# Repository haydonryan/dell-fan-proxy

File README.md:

# Dell Fan controller

Arduino Mega Fan Controller Sheild For R7515, R540 non hot swap fans.

# Background
I run an R7515 in my homelab. It's in a separate room upstairs (from my office) with the door open, I can hear it from my office downstairs.  It makes the room unusable that it sits in.

At 43% FAN, I can barely hear it from downstairs, 35% is really not too bad, up close.

The minimum fan speed and therefore noise is designed for a datacenter next to other heat generating servers with no noise contstraints, not a room in a house.
Plus I've got some non dell hardware( like many others do in homelabs) that the idrac controller doesn't know how to talk to, so the idrac just ramps the fans up to compensate for that one device.

I also noticed that at idle (which the machine sits 90% of the time) there is a 3 degree C differential between inlet and outlet temp, with the cpu being nice and cool.

# Why
- Dell support told me I'm not using the server for it's use case (Datacenter usage) - They're correct.
- Don't want to modify the firmware (it's signed anyways)
- Thought this would be an interesting project tom get more into electronics and control boards.

- As these machines come out of primary service in datacenters people are going to want to lab them - let's give them the power to do that!

# Disclaimer
- Will void your warranty
- Could cause your server to overheat
- Improper connection of fans can short out your motherboard!!!

- No responsibility taken for damaged hardware, loss of income, etc.

# Bill Of Materials:
- 6 Molex 2.00mm 2 Row, 6 Position Rectangular Receptical (Part # 0511100660) ~80c each https://www.digikey.com/en/products/detail/molex/0511100660/1144838?s=N4IgTCBcDaIOoFkCMAOArAdgwWgHIBEQBdAXyA
- 36 Molex Connector Socket 24-30AWG Crimp Gold (Part # 0503948054) 5c each https://www.digikey.com/en/products/detail/molex/0503948054/2404822?s=N4IgTCBcDaIAwFY4GYCcAWAHI9IC6AvkA

- 6 Amphenol ICC Conenctor Through Header Vert 6 Ppos 2.00mm (Part # 98414-G06-06LF) https://www.digikey.com/en/products/detail/amphenol-icc-fci/98414-G06-06LF/1535247?s=N4IgTCBcDaIGwAYCcBaAzHMAOFA5AIiALoC%2BQA

- 1 Arduino Mega

- 24 AWG hookup wire - 5 colors preferred, but just be careful if you don't have different colors Cheaper on Amazon (https://www.amazon.com/CBAZYTM-Stranded-Flexible-Silicone-Electric/dp/B073RD76QD/ref=sr_1_22?dchild=1&keywords=24%2BAWG&qid=1606865665&s=hi&sr=1-22&th=1)

- 6 TMP36 Temperature Sensors?? ~$1.50 https://www.digikey.com/en/products/detail/analog-devices-inc/TMP36GT9Z/820404

- Shrink wrap for wires
  - https://www.amazon.com/Eventronic-200pcs-Shrink-Tubing-Tubes/dp/B087JHB2CL/ref=sr_1_68?dchild=1&keywords=shrink+wrap+tube&qid=1606867076&sr=8-68
  - https://www.amazon.com/High-Heat-Shrink-Tubing-Tube/dp/B0722HN8SW/ref=sr_1_80?dchild=1&keywords=shrink+wrap+tube&qid=1606867076&sr=8-80
  - https://www.mouser.com/ProductDetail/Qualtek/Q2-F-RK4-1-16-11-6IN-39?qs=f6iYHOF0qgRLREW66g%2FPwg%3D%3D&gclid=CjwKCAiA8Jf-BRB-EiwAWDtEGuuEjQNy0toZvRLEwSUv5-1h-9RVMS_Smtxu-MWcHakHl9INQqu-WxoCvIEQAvD_BwE

# Random bits of information

By measuring and pulling pins out of the fan, I was able to determine that the pins (with the plastic nib up, facing away from you in the order:
```
1   2   3
4   5   6
```

That the Wires are:

1. Blue - PWM
2. Not connected
3. Black - Ground
4. -| Red - 12v (this wire continues to fan)
5. -| Red - 12v Loopback
6. Yellow - Sense wire.

Arduino Pin	 Register
- 2	OCR3B
- 3	OCR3C
- 4	OCR4C
- 5	OCR3A
- 6	OCR4A
- 7	OCR4B
- 8	OCR4C
- 9	OCR2B
- 10	OCR2A
- 11	OCR1A
- 12	OCR1B
- 13	OCR0A
- 44	OCR5C
- 45	OCR5B
- 46	OCR5A

source: http://astro.neutral.org/arduino/arduino-pwm-pins-frequency.shtml

## Fri Dec 31 11:26:19 2021
Checked the continuity - on the new server board - there's a common 12v rail AND common 12v ground.  This means that I can easily check the fan project using the bench power supply.

So far so good on the server. Printed U shaped spacers to save the cables for fans 1-3.  Definitely prefer to do this over not having anything pushing the top up.

I did find that only fan 3 has 12v power when powered off, the rest must be switched somewhere in the motherboard.

Cable lengths:
- Fan 1 30cm
- Fan 2 26cm
- Fan 3 45cm
- Fan 4 40cm
- Fan 5 35cm
- Fan 6 40cm

Max length shrink tubing at the arduino end: 1-1.5cm

# July 2022 Update
I've been testing this during summer and noticed that as the inlet temperature approaches the limit "for this configuration" the fans ramp significantly.  This is clearly a preventative reaction rather than a reactive one.  Also ensuring that the hardware that is in the server is "compatilbe" aka listed on the compatabilty matrix certainly helps to reduce the speed of the fans.

# May 2024 Update
Have been running my server 24/7 for two years now with no ill effects.  No hardware failures, and just less noise.  It's not perfect and fans seem to surge slightly vs stay flat consistently.  It's not too big of an issue and could probably be adjusted by increasing the time the fans are averaged. Very happy with how this project is running.

# Making cable tips.
Put some shrink tubing on the 12v wire on the loop and the main wire before putting the terminal into the block. Stray 12v is SUPER bad.
Cut the terminal off the tape but leave the small bit of tape on for holding it steady.
put the terminal into the 1.3mm crimp size first all the way up to the tape - it should hold itself in there - making it easier to feed in the cable(s).

Make sure to crimp the actual insulation.
Don't have the wire come out too far as mounting this, the pins will potentially pus the pin out if there's not enough space.
https://www.youtube.com/watch?v=Ta55NTSBLN0

Do the dual power lead crimp first (it's the hardest)

# Possible improvements
It would be much safer to map the fan speed returned to idrac from the detected speed of the fan, not the requested rpm. That way if a fan fails, then idrac will throw a fault.

# Compatability
## Compatible Dell Servers
- R7515 (tested)
- R540 (untested)
- R7415 (untested)

## Incompatible Dell Servers
- R740 / R740XD
- R840
- R7615
- R550
- (anything where the fan plugs directly into the motherboard)

## Unsure
- R240 (unsure if can fit)
- R340 (unsure if can fit)
- R640 (unsure if can fit)

# Resources:
- Starting point: https://www.youtube.com/watch?v=UJK2JF8wOu8
- Replacement Fan: https://www.itcreations.com/product/119156
- Standard 4 pin fan pinout https://allpinouts.org/pinouts/connectors/motherboards/motherboard-cpu-4-pin-fan/
- https://pastebin.com/s49SWw1A
- https://github.com/Max-Sum/HP-fan-proxy/blob/master/hp_fan.ino
- https://www.avdweb.nl/arduino/misc/handy-functions
- https://www.reddit.com/r/homelab/comments/8wbogx/my_attempt_at_creating_a_circuit_board_that/
- https://www.reddit.com/r/homelab/comments/beuks5/silencing_the_hp_dl380_for_good/

- Setting the interrupt priority: https://www.youtube.com/watch?v=H3o08WE0zEI
- Delta Fan Datasheet for similar fan: https://www.mouser.com/datasheet/2/632/dele_s_a0011169984_1-2290125.pdf
- https://homeservershow.com/forums/topic/7294-faking-the-fan-signal/

- https://forum.arduino.cc/t/problem-measuring-4-pin-fan-rpm/666804/6
- http://www.benripley.com/diy/arduino/three-ways-to-read-a-pwm-signal-with-arduino/
- https://www.youtube.com/watch?v=nut1ZiiXzVU&t=143s

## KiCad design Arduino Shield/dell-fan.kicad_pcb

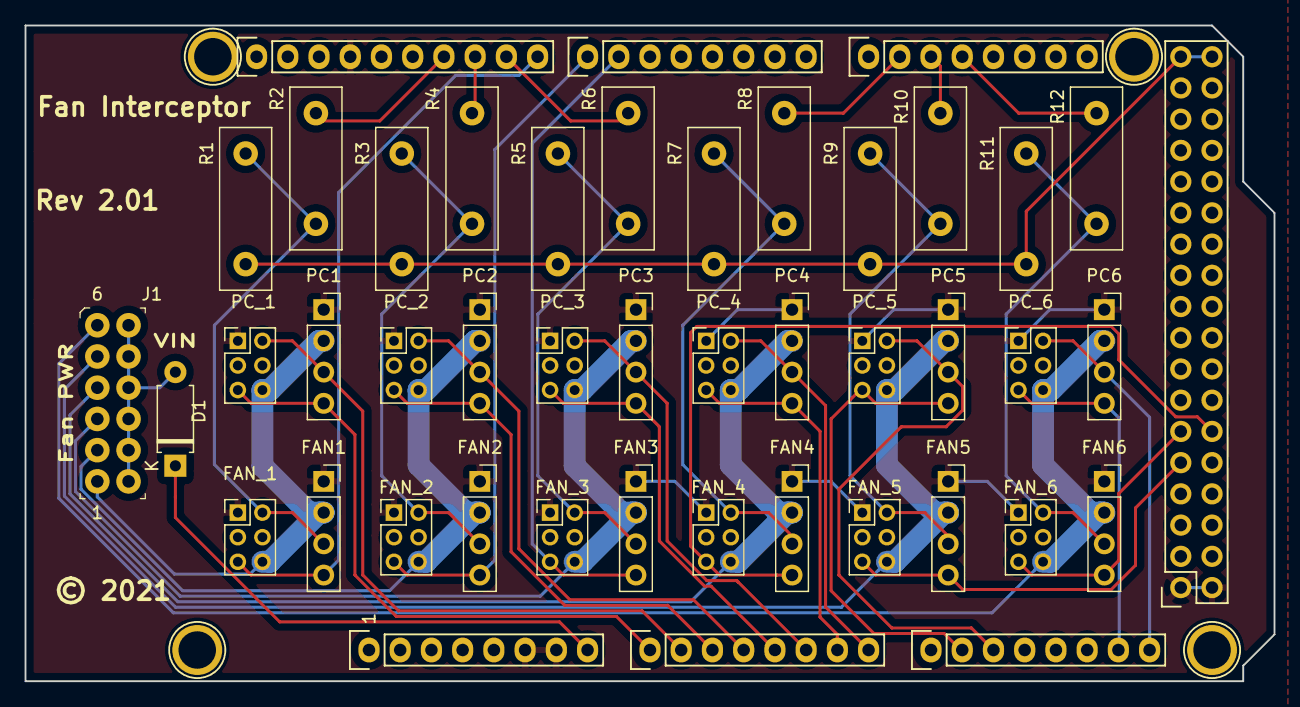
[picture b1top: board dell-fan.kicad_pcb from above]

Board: 2 copper layers, 101.6 x 53.3 mm, 49 parts (0 on the bottom side), 40 nets.

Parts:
D1: 1N4007; D_A-405_P7.62mm_Horizontal
FAN1, FAN2, FAN3, FAN4, FAN5, FAN6: To Fan; PinSocket_1x04_P2.54mm_Vertical
FAN_1, FAN_2, FAN_3, FAN_4, FAN_5, FAN_6: To FAN; PinHeader_2x03_P2.00mm_Vertical
J1: Power; PinHeader_6x2_P2.54mm_Horizontal
P1: Digital; Socket_Strip_Arduino_2x18
P2: Power; Socket_Strip_Arduino_1x08
P3, P4: Analog; Socket_Strip_Arduino_1x08
P5: PWM; Socket_Strip_Arduino_1x10
P6: PWM; Socket_Strip_Arduino_1x08
P7: Communication; Socket_Strip_Arduino_1x08
P8, P10, P11, P13: CONN_01X01; Arduino_1pin
PC1, PC2, PC3, PC4, PC5, PC6: To PC; PinSocket_1x04_P2.54mm_Vertical
PC_1, PC_2, PC_3, PC_4, PC_5, PC_6: To PC; PinHeader_2x03_P2.00mm_Vertical
R1, R3, R5, R7, R9, R11: 10k; R_Box_L13.0mm_W4.0mm_P9.00mm
R2, R4, R6, R8, R10, R12: 220k; R_Box_L13.0mm_W4.0mm_P9.00mm

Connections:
+5V: P1.35, P1.36, R1.2, R3.2, R5.2, R7.2, R9.2, R11.2
/Vin: D1.1, P2.8
FAN1_12v: FAN1.2, FAN_1.6, J1.11, PC1.2, PC_1.6
FAN1_PWM: FAN1.4, FAN_1.5, P5.10
FAN1_TACH: P5.7, R2.2
FAN1_TACH_IN: FAN1.3, FAN_1.2, R1.1, R2.1
FAN2_12v: FAN2.2, FAN_2.6, J1.9, PC2.2, PC_2.6
FAN2_PWM: FAN2.4, FAN_2.5, P6.1
FAN2_TACH: P5.8, R4.2
FAN2_TACH_IN: FAN2.3, FAN_2.2, R3.1, R4.1
FAN3_12v: FAN3.2, FAN_3.6, J1.7, PC3.2, PC_3.6
FAN3_PWM: FAN3.4, FAN_3.5, P6.2
FAN3_TACH: P5.9, R6.2
FAN3_TACH_IN: FAN3.3, FAN_3.2, R5.1, R6.1
FAN4_12v: FAN4.2, FAN_4.6, J1.5, PC4.2, PC_4.6
FAN4_PWM: FAN4.4, FAN_4.5, P1.12
FAN4_TACH: P7.2, R8.2
FAN4_TACH_IN: FAN4.3, FAN_4.2, R7.1, R8.1
FAN5_12v: FAN5.2, FAN_5.6, J1.3, PC5.2, PC_5.6
FAN5_PWM: FAN5.4, FAN_5.5, P1.9
FAN5_TACH: P7.3, R10.2
FAN5_TACH_IN: FAN5.3, FAN_5.2, R9.1, R10.1
FAN6_12v: FAN6.2, FAN_6.6, J1.1, PC6.2, PC_6.6
FAN6_PWM: FAN6.4, FAN_6.5, P1.11
FAN6_TACH: P7.4, R12.2
FAN6_TACH_IN: FAN6.3, FAN_6.2, R11.1, R12.1
GND: FAN1.1, FAN2.1, FAN3.1, FAN4.1, FAN5.1, FAN6.1, FAN_1.1, FAN_2.1, FAN_3.1, FAN_4.1, FAN_5.1, FAN_6.1, P1.1, P1.2, P2.6, P2.7, P5.4, PC1.1, PC2.1, PC3.1, PC4.1, PC5.1, PC6.1, PC_1.1, PC_2.1, PC_3.1, PC_4.1, PC_5.1, PC_6.1
unnamed: D1.2, J1.2, J1.4, J1.6, J1.8, J1.10, J1.12
PC1_PWM: P3.1, PC1.4, PC_1.5
PC1_TACH: P3.2, PC1.3, PC_1.2
PC2_PWM: P3.3, PC2.4, PC_2.5
PC2_TACH: P3.4, PC2.3, PC_2.2
PC3_PWM: P3.5, PC3.4, PC_3.5
PC3_TACH: P3.6, PC3.3, PC_3.2
PC4_PWM: P3.7, PC4.4, PC_4.5
PC4_TACH: P3.8, PC4.3, PC_4.2
PC5_PWM: P4.2, PC5.4, PC_5.5
PC5_TACH: P4.3, PC5.3, PC_5.2
PC6_PWM: P4.7, PC6.4, PC_6.5
PC6_TACH: P4.8, PC6.3, PC_6.2

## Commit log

2021-08-04 adding some comments, fixing some code formatting, and variable for clarity
2021-08-13 updating readme
2021-08-13 cleaning up
2021-08-13 Cleanup. PC interface. Helper func. 6 fan support
    I realize I haven't commited for a while, so need to fix that -
    committing now. Added a few helper functions
2021-08-13 moving tick start time variable into data structure
2021-08-13 changed fan_rpm to int
2021-08-13 moving rpm, and interrupt count to data structure
2021-08-13 Cleanup and adding some comments
2021-08-13 moving open drain var into datastructure
2021-08-13 formatting...
2021-08-13 added read_idrac_pwm function + formatting
2021-08-13 made passthrough to fan, improved output and cleanup
2021-08-13 map requested pwm through fan curve map
2021-08-13 correcting tach calculation to follow actual fan rpm
2021-08-13 moving setting OCR1A to correct locations
2021-08-13 more cleanup and formatting
2021-08-13 adding RPM map to fake to idrac
2021-08-13 adding mapping for tach output to idrac and removing test using internal pullup that failed
2021-09-02 changing wire for arduino mega
2021-09-02 making fan interrupt count volatile
2021-09-02 correcting fan pwm
2021-09-07 creating makefile for sketch
2021-09-07 creating helper script to display serial output
2021-09-11 expanding pin consts to support 6 fans
2021-09-11 moving comment back
2021-09-11 adding additional interrupt callback functions
2021-09-11 adding comment to specify what board to use
2021-09-11 improving comments
2021-09-13 updating comments
2021-09-13 changing to timer 5 - for ports 44, 45, 46
2021-09-13 Adding support for 3 fans
2021-09-13 adding 6 channel support for drain
2021-09-25 adding in PWM output to fan for all 6 fans
2021-09-25 setup interrupts to read from all channels
2021-09-26 cleanup
2021-09-26 making open drain work for all 6 channels
2021-09-26 fixing typo
2021-09-26 adding case where idrac pwm request is zero - don't run fans.
2021-10-04 updating comment to include wire colors
2021-10-04 updating fan curve
2021-10-19 adding average for idrac tach
2021-10-19 changing fans pins to suit board locations better
2021-10-19 reordering first 3 fans PWM to better suit board layout
2021-10-19 reordering second half of fan pwm pins to better suit board layout
2021-10-19 re-ordering fan tach pins to suit board layout
2021-10-19 initial commit of kicad arduino shield
2021-10-19 updating lcoation of PC pwm and tach signals for better board layout
2021-10-19 moved PC Tach and PWM to D554-d69
2021-10-19 fixed ground plane issue
2021-10-20 adding test code to count fan rpm not using interrupts
2021-10-20 fixing bug in insertion - this is why i should have had tests
2021-10-23 Switching from interrupts to reading using pulseIn with smoothing
2021-10-23 setting sane minimum fan speed
2021-10-23 No interrupts means better pin placement
2021-11-08 commiting prototype run with gerber files
2021-12-25 updating readme after fan controller failed
2022-01-04 fixing whitespace errors
2022-01-04 fixing whitespace
2022-01-04 fixing two missing traces from production prototype
2022-01-04 changing text to skilk screens
2022-01-04 removing labels from pin blocks
2022-01-05 making resistors larger
2022-01-05 removing ground link as the board uses a common ground
2022-01-05 updating resistor size in schematic
2022-01-05 removing ground link from pcb design
2022-01-05 fixing typo in fan speed source
2022-01-05 redesign for rev 2.01. Swapped PC and FAN location, and swapped FAN4_PWM and FAN5_PWM pins for simplicity
2022-03-08 increasing fanspeed while up and running
2022-03-31 adding more points to fan curve and increasing fan speed
2023-06-01 Adding project images
2023-06-01 Cleaning up README.md
2025-05-06 Added may update and compatability

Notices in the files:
Arduino Shield/dell-fan.kicad_pcb:
© 2021
